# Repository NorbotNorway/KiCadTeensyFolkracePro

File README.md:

# KiCadTeensyFolkracePro
PCB made with KiCad. For Teensy and i2c GP2Y... sensor

(The JST SH 1mm connectors are from http://www.kicadlib.org/)

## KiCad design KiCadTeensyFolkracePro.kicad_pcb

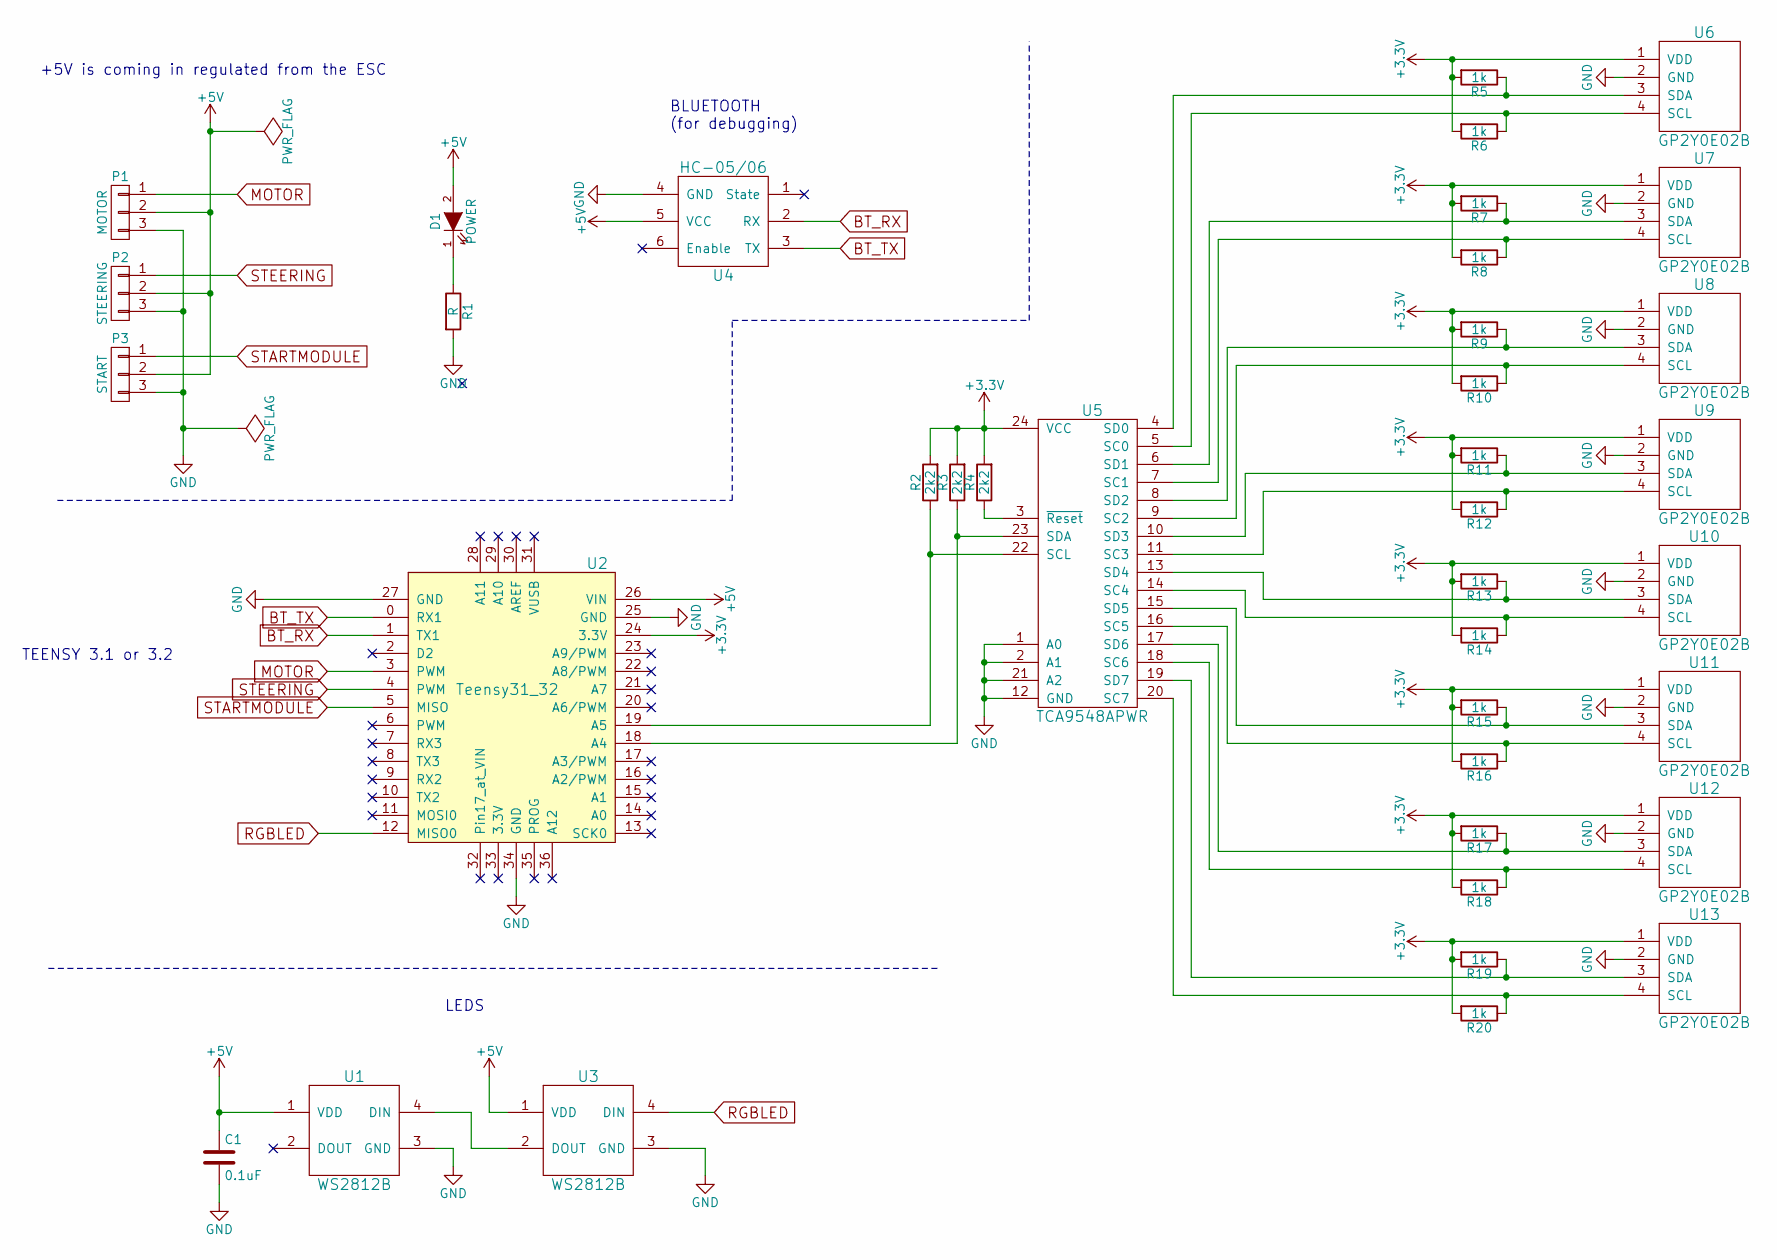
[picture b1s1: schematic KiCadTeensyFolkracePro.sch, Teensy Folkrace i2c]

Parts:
C1: 0.1uF; C_0805
D1: POWER; R_0603
P1: MOTOR; Pin_Header_Straight_1x03
P2: STEERING; Pin_Header_Straight_1x03
P3: START; Pin_Header_Straight_1x03
R1: R; R_0603
R2, R3, R4: 2k2; R_0603
R5, R6, R7, R8, R9, R10, R11, R12, R13, R14, R15, R16, R17, R18, R19, R20: 1k; R_0603
U1, U3: WS2812B
U2: Teensy31_32; Teensy-3.1_3.2
U4: HC-05/06; Pin_Header_Straight_1x06
U5: TCA9548APWR; TSSOP-24_4.4x7.8mm_Pitch0.65mm
U6, U7, U8, U9, U10, U11, U12, U13: GP2Y0E02B; JST-BM-04B-SRSS-TB

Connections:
+3V3: R2.2, R3.2, R4.2, R5.2, R6.2, R7.2, R8.2, R9.2, R10.2, R11.2, R12.2, R13.2, R14.2, R15.2, R16.2, R17.2, R18.2, R19.2, R20.2, U2.24 (3.3V), U5.24 (VCC), U6.1 (VDD), U7.1 (VDD), U8.1 (VDD), U9.1 (VDD), U10.1 (VDD), U11.1 (VDD), U12.1 (VDD), U13.1 (VDD)
+5V: C1.1, D1.2 (A), P1.2, P2.2, P3.2, U1.1 (VDD), U2.26 (VIN), U3.1 (VDD), U4.5 (VCC)
BT_RX: U2.1 (TX1), U4.2 (RX)
BT_TX: U2.0 (RX1), U4.3 (TX)
GND: C1.2, P1.3, P2.3, P3.3, R1.2, U1.3 (GND), U2.25 (GND), U2.27 (GND), U2.34 (GND), U3.3 (GND), U4.4 (GND), U5.1 (A0), U5.2 (A1), U5.12 (GND), U5.21 (A2), U6.2 (GND), U7.2 (GND), U8.2 (GND), U9.2 (GND), U10.2 (GND), U11.2 (GND), U12.2 (GND), U13.2 (GND)
MOTOR: P1.1, U2.3 (PWM)
unnamed: D1.1 (K), R1.1
unnamed: R2.1, U2.19 (A5), U5.22 (SCL)
unnamed: R3.1, U2.18 (A4), U5.23 (SDA)
unnamed: R4.1, U5.3 (~Reset)
unnamed: R5.1, U5.4 (SD0), U6.3 (SDA)
unnamed: R6.1, U5.5 (SC0), U6.4 (SCL)
unnamed: R7.1, U5.6 (SD1), U7.3 (SDA)
unnamed: R8.1, U5.7 (SC1), U7.4 (SCL)
unnamed: R9.1, U5.8 (SD2), U8.3 (SDA)
unnamed: R10.1, U5.9 (SC2), U8.4 (SCL)
unnamed: R11.1, U5.10 (SD3), U9.3 (SDA)
unnamed: R12.1, U5.11 (SC3), U9.4 (SCL)
unnamed: R13.1, U5.13 (SD4), U10.3 (SDA)
unnamed: R14.1, U5.14 (SC4), U10.4 (SCL)
unnamed: R15.1, U5.15 (SD5), U11.3 (SDA)
unnamed: R16.1, U5.16 (SC5), U11.4 (SCL)
unnamed: R17.1, U5.17 (SD6), U12.3 (SDA)
unnamed: R18.1, U5.18 (SC6), U12.4 (SCL)
unnamed: R19.1, U5.19 (SD7), U13.3 (SDA)
unnamed: R20.1, U5.20 (SC7), U13.4 (SCL)
unnamed: U1.4 (DIN), U3.2 (DOUT)
RGBLED: U2.12 (MISO0), U3.4 (DIN)
STARTMODULE: P3.1, U2.5 (MISO)
STEERING: P2.1, U2.4 (PWM)

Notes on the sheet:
+5V is coming in regulated from the ESC
BLUETOOTH (for debugging)
LEDS
TEENSY 3.1 or 3.2

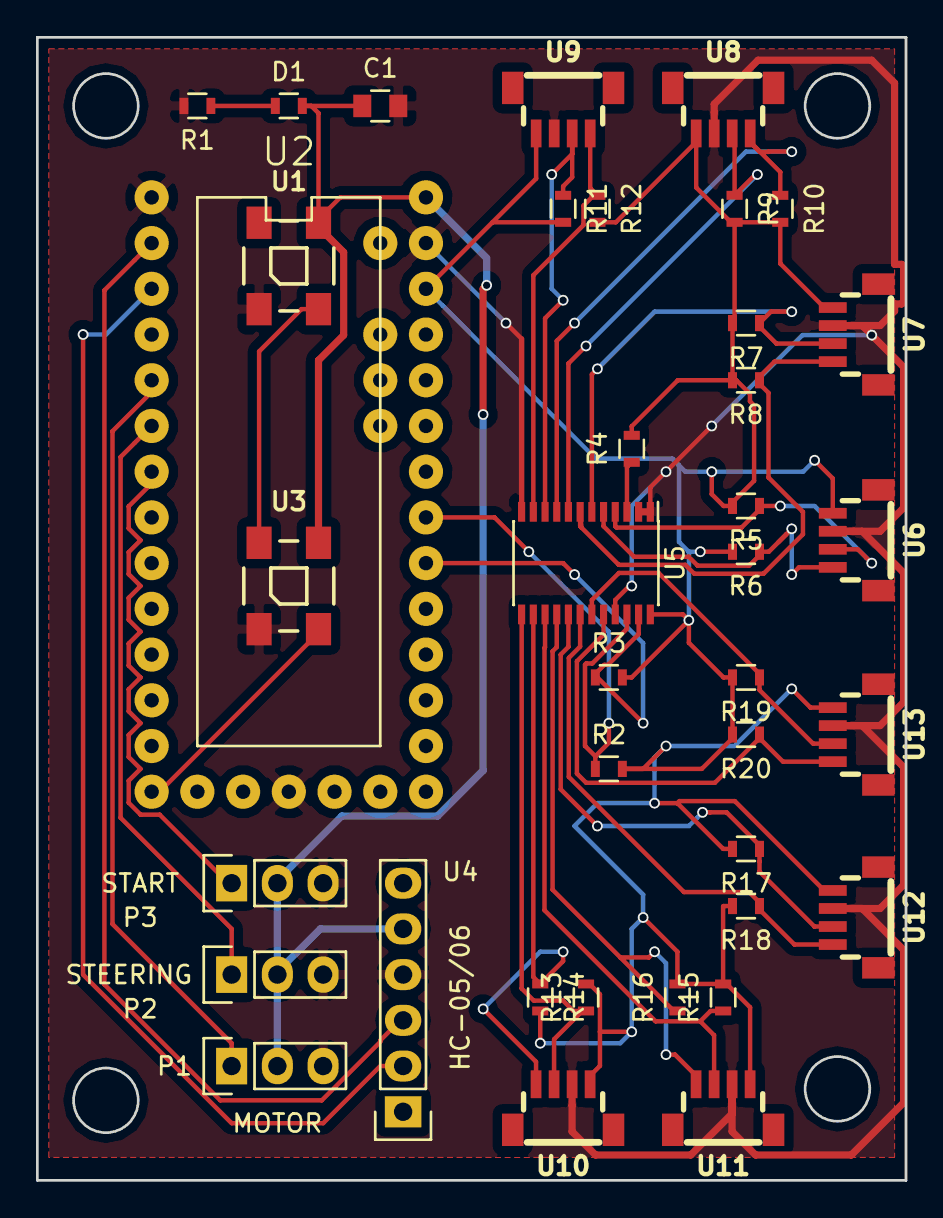
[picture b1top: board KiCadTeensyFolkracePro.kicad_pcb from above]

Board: 2 copper layers, 48.3 x 63.5 mm, 38 parts (0 on the bottom side), 30 nets.

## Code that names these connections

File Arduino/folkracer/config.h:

//Define address location in EEPROM for each variable
#define SETTING_SPEED 1
#define SETTING_MAX_SPEED 2 //Set the maximum speed of the motor, in percentage
#define SETTING_AVG 3
#define SETTING_DISABLE_MOTOR 4 //Set to something other than 0 to disable motor.
#define SETTING_PLOT_SPEED 5    //If set then write speeds to Serial for plotting
#define SETTING_PLOT_SENSORS 6  //If set then write sensorvalues to Serial for plotting
#define SETTING_STEERING_MIN 7  //us, NB two bytes!
#define SETTING_STEERING_MAX 9  //us, NB two bytes!
#define SETTING_CRASH_DIST 11   //cm, centimeters to wall from front sensor for detecting crash
#define SETTING_MIN_SPEED 12    //The minimum speed before motor stalls. Do not go slower than this.
#define SETTING_TURN_GAIN 13    //Multiplier for steering. Higher number gives more agressive turning.
#define SETTING_LOOP_DELAY 14   //Milliseconds to delay each loop
#define SETTING_REDUCE_SPEED_ANGLE 15 //Angle (degrees) which causes car to go at slower speed
#define SETTING_REDUCE_SPEED_BY 16  //Multiplier used to reduce speed while turning. F.ex 2 will half the speed.
#define SETTING_REVERSE_SPEED 17  //Speed to use when reversing

//TCA9548APWR (https://learn.adafruit.com/adafruit-tca9548a-1-to-8-i2c-multiplexer-breakout?view=all)
#define TCA_ADDRESS 0x70

//const int SERVO_STEERING_MIN = 1300; //us
//const int SERVO_STEERING_MAX = 1700; //us
const int SERVO_MOTOR_MAX = 1900;
const int SERVO_MOTOR_MIN = 1100;
const int LED_SLOW_BLINK = 800; //ms
const int LED_FAST_BLINK = 100; //ms

//Serial
const int SERIAL_BAUD_USB = 9600;
const int SERIAL_BAUD_BLUETOOTH = 9600;

//Pins
const int LED_PIN = 13;
const int SERVO_MOTOR_PIN = 3;
const int SERVO_STEERING_PIN = 4;
const int STARTMODULE_PIN = 5;

//Startmodule
enum startmoduleStates {
  WAITING,
  RUNNING,
  STOP,
  MANUAL
};

/*
//http://forum.arduino.cc/index.php/topic,44702.0.html
template <class T> int EEPROM_writeAnything(int ee, const T& value)
{
   const byte* p = (const byte*)(const void*)&value;
   int i(0);
   for (; i < sizeof(value); ++i)
       EEPROM.write(ee++, *p++);
   return i;
}


template <class T> int EEPROM_readAnything(int ee, T& value)
{
   byte* p = (byte*)(void*)&value;
   int i (0);
   for (; i < sizeof(value); ++i)
       *p++ = EEPROM.read(ee++);
   return i;
}
*/

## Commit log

2016-03-25 Initial
2016-04-30 Arduino files
2016-04-30 Simple bluetooth works
2016-04-30 Bluetooth still works
2016-04-30 Commands and TCA works
2016-04-30 EEPROM works
2016-05-01 Plotting from all three sensors works
2016-05-01 Trying to get Moving Average to work. Not stable yet.
2016-05-01 Started on Steering.
2016-05-01 Command 'steering' works. Fixed 'led.blink' command.
2016-05-01 Minor changes
2016-05-01 Motor works
2016-05-01 Added state handling
2016-05-02 Started testdriving
2016-05-02 Added interrupt for startmodule. Doesn't work yet.
2016-05-04 Can set maxspeed and disablemotor via configuration
2016-05-04 Minor changes while testing steering
2016-05-05 Lots of configurable configs!
2016-05-05 From Hackerparty
2016-05-06 Configurable turngain, loopdelay, reducespeedangle, reducespeedby
2016-05-27 Changes made in Gothenburg
2016-06-06 Minor
2016-07-23 Schematic added
